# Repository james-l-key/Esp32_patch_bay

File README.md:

# Esp32_Patch_Bay

## Warning! 

This project is in active hardware and software development. Things may change drastically at a moments notice.

An 8-pedal mono guitar patch bay controlled by an ESP32-S3, allowing dynamic reconfiguration of guitar pedal signal chains via a user interface with an OLED display and push buttons. The project uses analog multiplexers (CD4051B, ADG419BN) and op-amps (TL072) to route audio signals, controlled through shift registers (74HC595) interfaced with the ESP32-S3. The schematic is designed in KiCad 9.0, and the firmware is developed using the ESP-IDF framework.

## Table of Contents
- [Esp32\_Patch\_Bay](#esp32_patch_bay)
  - [Table of Contents](#table-of-contents)
  - [Features](#features)
  - [Hardware](#hardware)
  - [Software](#software)
  - [Installation](#installation)
  - [Usage](#usage)
  - [Project Structure](#project-structure)
  - [Contributing](#contributing)
  - [Issues](#issues)
  - [License](#license)
  - [Acknowledgements](#acknowledgements)

## Features
- **Dynamic Signal Routing**: Reconfigure the signal chain for up to 8 mono guitar pedals using a 9x8 matrix.
- **User Interface**: SSD1306/SH1106 OLED display for configuration feedback, with three push buttons (Program, Pedal 1, Pedal 2) and a Program Mode LED.
- **Low-Latency Audio**: CD4051B and ADG419BN analog multiplexers and TL072 op-amps ensure clean, buffered audio signal routing.
- **ESP32-S3 Control**: High-performance microcontroller for real-time control, programmed via ESP-IDF.
- **Extensible Design**: Easily scalable to support more pedals by adding multiplexers and shift registers.
- **Open Source**: Full schematic (`circuit.kicad_sch`), PCB layout, and firmware provided.

## Hardware
The patch bay is built around an **ESP32-S3** microcontroller and uses analog multiplexers for audio routing. For the complete hardware details, including the **schematic**, **PCB layout**, and **Bill of Materials (BOM)**, please see the dedicated [hardware repository](https://github.com/your-username/esp32_patch_bay_hardware).

## Software
The firmware is written in C using the **ESP-IDF** framework (v5.1 or later) for the ESP32-S3. Key components include:
- **Matrix Control**: `matrix.c` manages the 9x8 signal routing matrix, interfacing with 74HC595 shift registers to set analog switch states.
- **OLED Driver**: Displays the current signal chain and configuration status.
- **Button Handling**: Debounced inputs for Program, Pedal 1, and Pedal 2 buttons to navigate and set configurations.
- **LED Control**: Toggles the Program Mode LED based on user interaction.

### Dependencies
- **ESP-IDF**: Install ESP-IDF v5.1 or later (see [Espressif Documentation](https://docs.espressif.com/projects/esp-idf/en/latest/esp32s3/)).
- **KiCad 9.0**: For viewing/editing the schematic (`circuit.kicad_sch`).
- **I2C Library**: For SSD1306/SH1106 OLED communication (included in ESP-IDF).
- **GPIO Drivers**: Standard ESP-IDF GPIO functions for buttons, LED, and shift registers.

## Installation
### Prerequisites
- **Hardware**:
  - ESP32-S3 development board or custom PCB with the components listed above.
  - 1/4” mono jacks, buttons, LED, resistors (220Ω for LED, 4.7kΩ for pull-ups), and capacitors.
  - ±9V power supply or charge pump circuit.
- **Software**:
  - [ESP-IDF](https://docs.espressif.com/projects/esp-idf/en/latest/esp32s3/get-started/index.html) installed and configured.
  - [KiCad 9.0](https://www.kicad.org/download/) for schematic/PCB design.
  - A C compiler (e.g., `xtensa-esp32s3-elf-gcc`) included with ESP-IDF.
  - Python 3 for ESP-IDF build scripts.

### Steps
1. **Clone the Repository**:
   ```bash
   git clone [https://github.com/phi/Esp32_patch_bay.git](https://github.com/phi/Esp32_patch_bay.git)
   cd Esp32_patch_bay
   
2. **Set Up ESP-IDF**:
        Follow the ESP-IDF Getting Started Guide.
        Ensure the idf.py tool is accessible in your terminal.

3. **Build the Firmware**:
    ```bash
    idf.py set-target esp32s3
    idf.py build
   
5. **Flash the Firmware**:

    Connect the ESP32-S3 to your computer via USB.
    Flash the firmware:
    ```bash

        idf.py -p /dev/ttyUSB0 flash

  Replace /dev/ttyUSB0 with your serial port (e.g., COM3 on Windows).

  6. **Open the Schematic**:
        Launch KiCad 9.0.
        Open circuit.kicad_sch from the repository root.
        Verify connections and assign footprints for PCB layout.

   7. **Assemble the Hardware**:
        Solder components onto a PCB or prototype board based on the schematic.
        Connect 1/4” jacks to guitar, pedals, and amplifier.
        Power the circuit with +3.3V and ±9V supplies.

## Usage

  **Power On**:
        Connect the patch bay to power (+3.3V, ±9V).
        The OLED displays the current signal chain (e.g., Guitar → Pedal 1 → Pedal 2 → Amp).

  **Program Mode**:
        Press the Program button (SW1) to enter Program Mode (LED1 lights up).
        Use Pedal 1 (SW2) and Pedal 2 (SW3) buttons to select the desired signal path.
        Press Program again to save and exit.

  **Signal Routing**:
        The ESP32-S3 updates the 74HC595 shift registers, which set the analog switches to route the audio signal.
        TL072 op-amps buffer the input and output to maintain signal integrity.

  **Monitor**:
        Use the OLED to confirm the signal chain.
        Check the serial output (via idf.py monitor) for debugging.

***Example Signal Chains***

  * Bypass: Guitar → Amp.
  * Single Pedal: Guitar → Pedal 1 → Amp.
  * Dual Pedal: Guitar → Pedal 1 → Pedal 7 → Amp or Guitar → Pedal 2 → Pedal 1 → Amp.

## Project Structure

```md
Esp32_patch_bay/
├── circuit.kicad_sch        # KiCad 9.0 schematic for 3x3 matrix (scalable to 9x8)
├── main/
│   ├── main.c               # Entry point for ESP-IDF firmware
│   ├── matrix.c             # Signal routing matrix control
│   ├── matrix.h             # Header for matrix functions
│   ├── oled.c               # OLED display driver
│   ├── oled.h               # Header for OLED functions
├── CMakeLists.txt           # ESP-IDF project configuration
├── README.md                # This file
├── LICENSE                  # License file (e.g., MIT)
└── docs/
    ├── HARDWARE.md          # Detailed hardware setup
    ├── SOFTWARE.md          # Firmware development guide
    ├── TROUBLESHOOTING.md   # Common issues and solutions
```
## Scaling to 8 Pedals

**The current schematic implements a 9x8 matrix (Guitar In, Amp Out, and 8 pedals In/Out).**

## Contributing

**Contributions are welcome! To contribute**:

  Fork the repository.
  Create a branch (git checkout -b feature/your-feature).
  Commit changes (git commit -m "Add your feature").
  Push to the branch (git push origin feature/your-feature).
  Open a Pull Request.

## Issues

  Report bugs or suggest features via the Issues tab.
  Include reproduction steps and relevant logs (e.g., idf.py monitor output).

## License

This project is licensed under the MIT License. See the [LICENSE](LICENSE) file for details.

## Acknowledgements

  Espressif Systems for the ESP-IDF framework and ESP32-S3.
  KiCad for open-source EDA tools.
  Community: Inspiration from guitar pedalboard designs and open-source hardware projects.

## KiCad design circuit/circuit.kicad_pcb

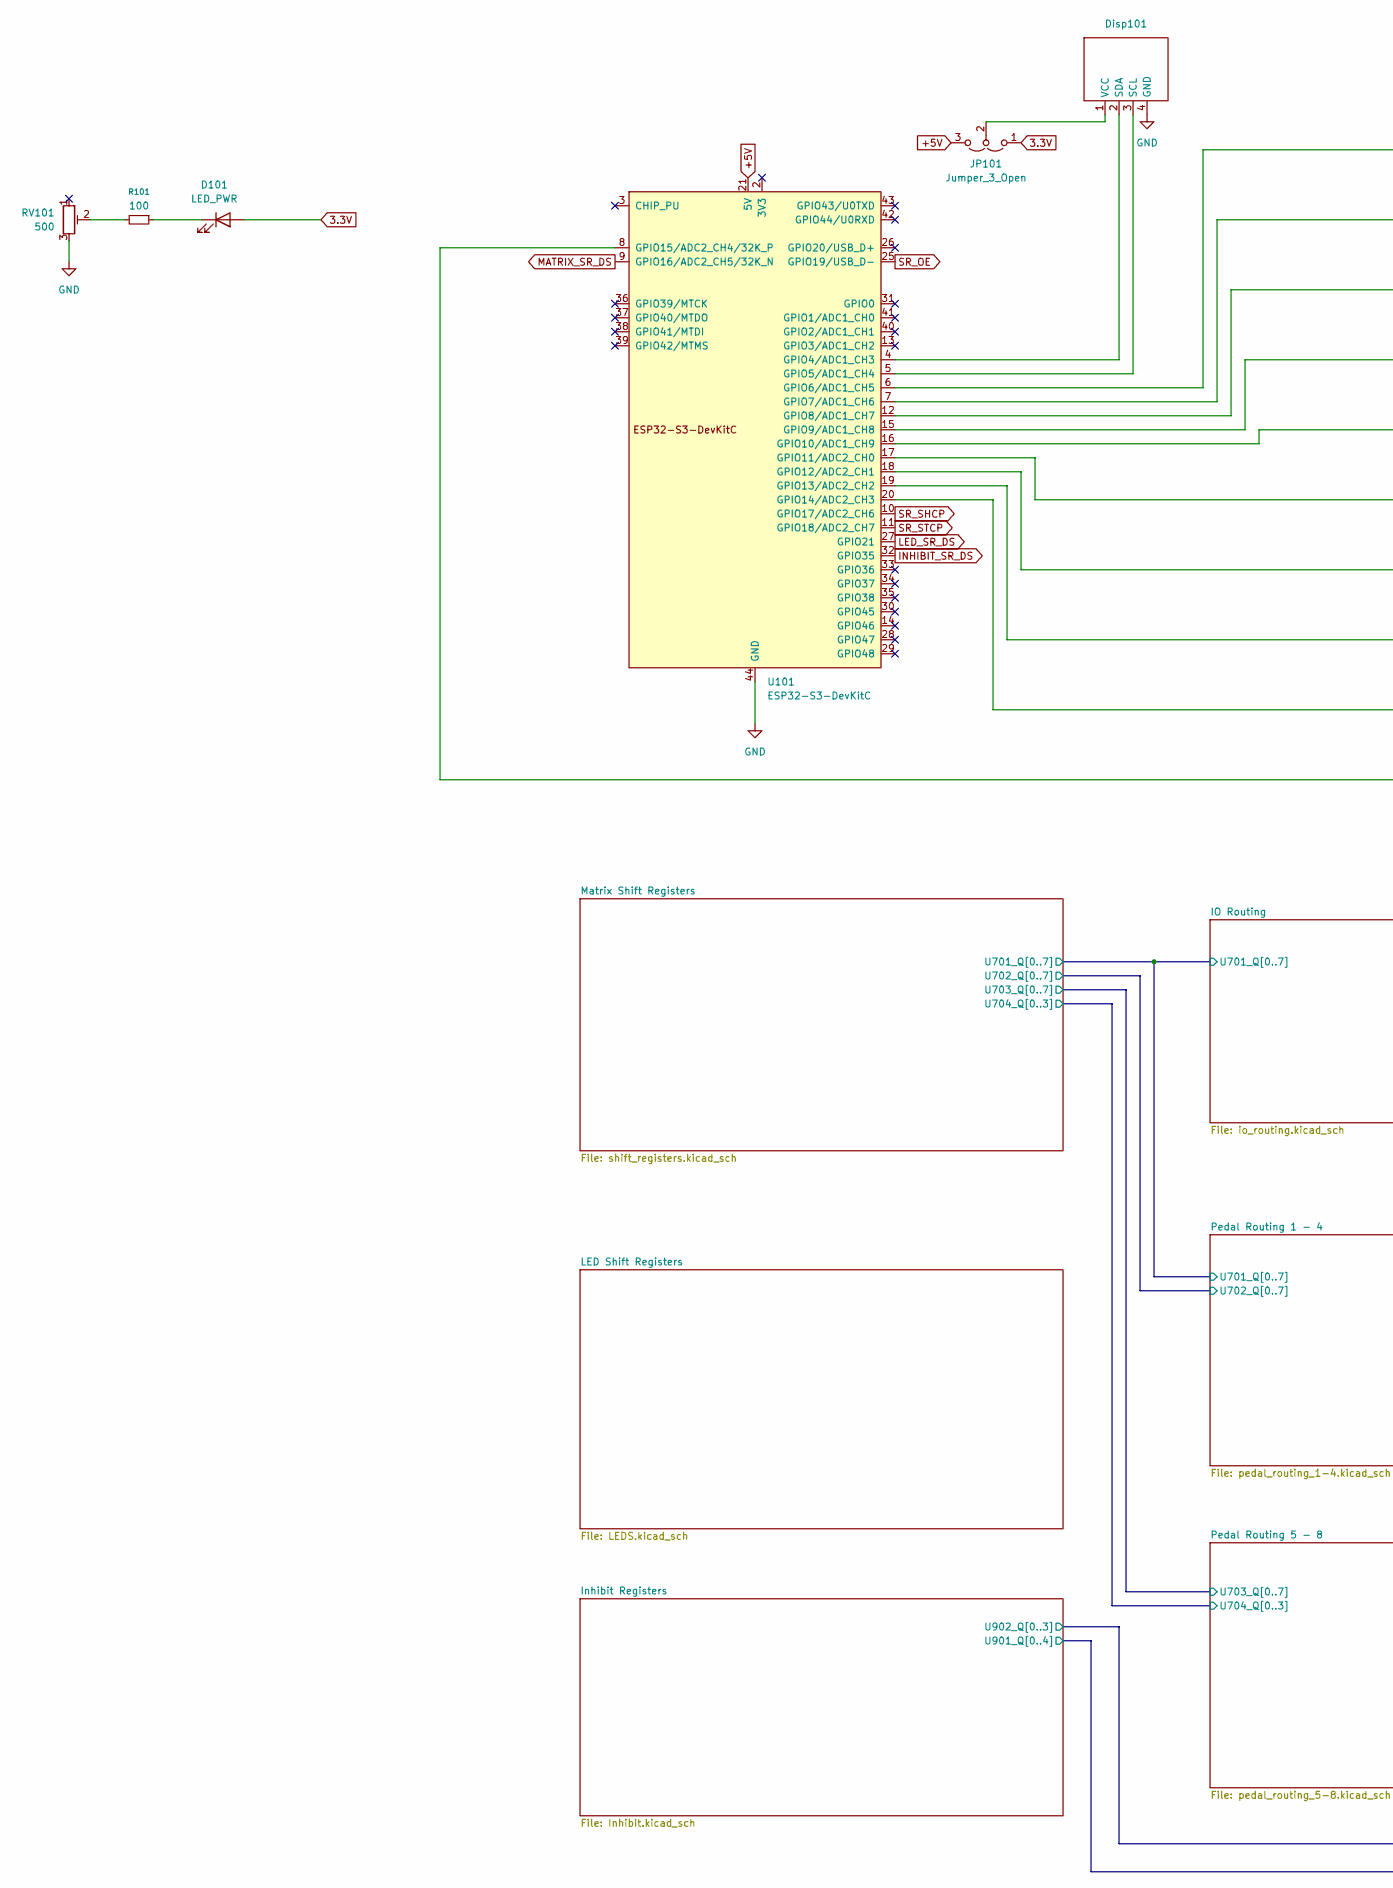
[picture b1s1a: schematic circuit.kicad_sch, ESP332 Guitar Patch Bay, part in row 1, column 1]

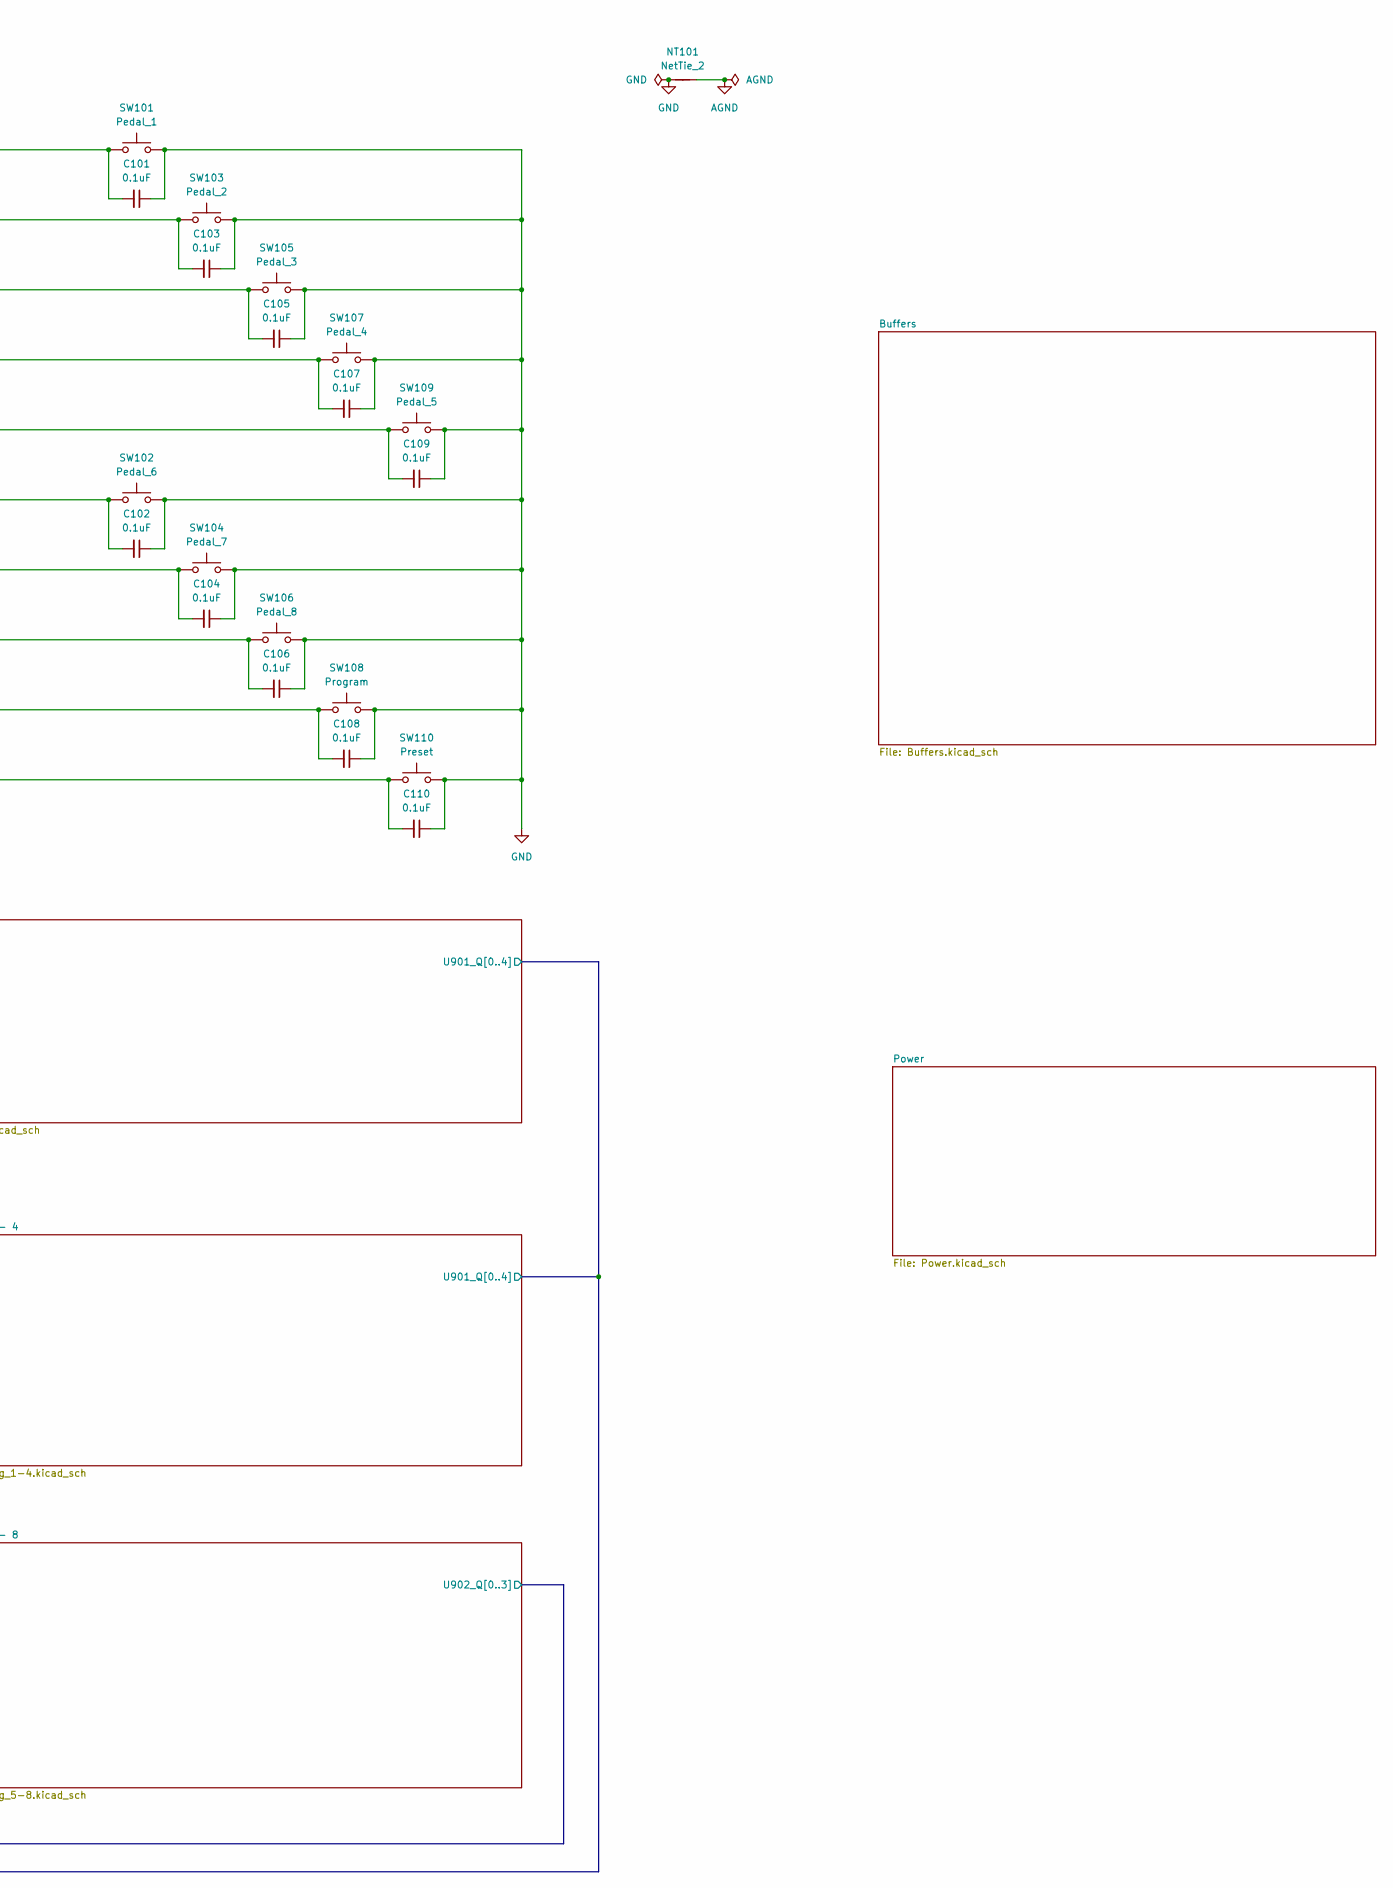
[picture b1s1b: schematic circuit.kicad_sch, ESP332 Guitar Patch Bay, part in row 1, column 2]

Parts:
C101, C102, C103, C104, C105, C106, C107, C108, C109, C110: 0.1uF; C_Disc_D5.0mm_W2.5mm_P2.50mm
D101: LED_PWR; PinHeader_1x02_P2.54mm_Vertical
Disp101: PinHeader_1x04_P2.54mm_Vertical
JP101: Jumper_3_Open; PinSocket_1x03_P2.54mm_Vertical
NT101: NetTie_2; NetTie-2_THT_Pad1.0mm
R101: 100; R_Axial_DIN0207_L6.3mm_D2.5mm_P7.62mm_Horizontal
RV101: 500; Potentiometer_Bourns_3339P_Vertical
SW101: Pedal_1; PinHeader_1x02_P2.54mm_Vertical
SW102: Pedal_6; PinHeader_1x02_P2.54mm_Vertical
SW103: Pedal_2; PinHeader_1x02_P2.54mm_Vertical
SW104: Pedal_7; PinHeader_1x02_P2.54mm_Vertical
SW105: Pedal_3; PinHeader_1x02_P2.54mm_Vertical
SW106: Pedal_8; PinHeader_1x02_P2.54mm_Vertical
SW107: Pedal_4; PinHeader_1x02_P2.54mm_Vertical
SW108: Program; PinHeader_1x02_P2.54mm_Vertical
SW109: Pedal_5; PinHeader_1x02_P2.54mm_Vertical
SW110: Preset; PinHeader_1x02_P2.54mm_Vertical
U101: ESP32-S3-DevKitC

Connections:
3.3V: D101.2 (A), JP101.1 (A); also elsewhere on the board
+5V: JP101.3 (B), U101.21 (5V); also elsewhere on the board
AGND: NT101.2; also elsewhere on the board
GND: C101.1, C102.1, C103.1, C104.1, C105.1, C106.1, C107.1, C108.1, C109.1, C110.1, Disp101.4 (GND), NT101.1, RV101.3, SW101.2, SW102.2, SW103.2, SW104.2, SW105.2, SW106.2, SW107.2, SW108.2, SW109.2, SW110.2, U101.22 (GND), U101.23 (GND), U101.24 (GND), U101.44 (GND); also elsewhere on the board
INHIBIT_SR_DS: U101.32 (GPIO35); also elsewhere on the board
LED_SR_DS: U101.27 (GPIO21); also elsewhere on the board
MATRIX_SR_DS: U101.9 (GPIO16/ADC2_CH5/32K_N); also elsewhere on the board
unnamed: D101.1 (K), R101.1
unnamed: Disp101.3 (SCL), U101.5 (GPIO5/ADC1_CH4)
unnamed: Disp101.2 (SDA), U101.4 (GPIO4/ADC1_CH3)
unnamed: Disp101.1 (VCC), JP101.2 (C)
unnamed: R101.2, RV101.2
unnamed: C101.2, SW101.1, U101.6 (GPIO6/ADC1_CH5)
unnamed: C103.2, SW103.1, U101.7 (GPIO7/ADC1_CH6)
unnamed: C105.2, SW105.1, U101.12 (GPIO8/ADC1_CH7)
unnamed: C107.2, SW107.1, U101.15 (GPIO9/ADC1_CH8)
unnamed: C109.2, SW109.1, U101.16 (GPIO10/ADC1_CH9)
unnamed: C102.2, SW102.1, U101.17 (GPIO11/ADC2_CH0)
unnamed: C104.2, SW104.1, U101.18 (GPIO12/ADC2_CH1)
unnamed: C106.2, SW106.1, U101.19 (GPIO13/ADC2_CH2)
unnamed: C108.2, SW108.1, U101.20 (GPIO14/ADC2_CH3)
unnamed: C110.2, SW110.1, U101.8 (GPIO15/ADC2_CH4/32K_P)
SR_OE: U101.25 (GPIO19/USB_D-); also elsewhere on the board
SR_SHCP: U101.10 (GPIO17/ADC2_CH6); also elsewhere on the board
SR_STCP: U101.11 (GPIO18/ADC2_CH7); also elsewhere on the board

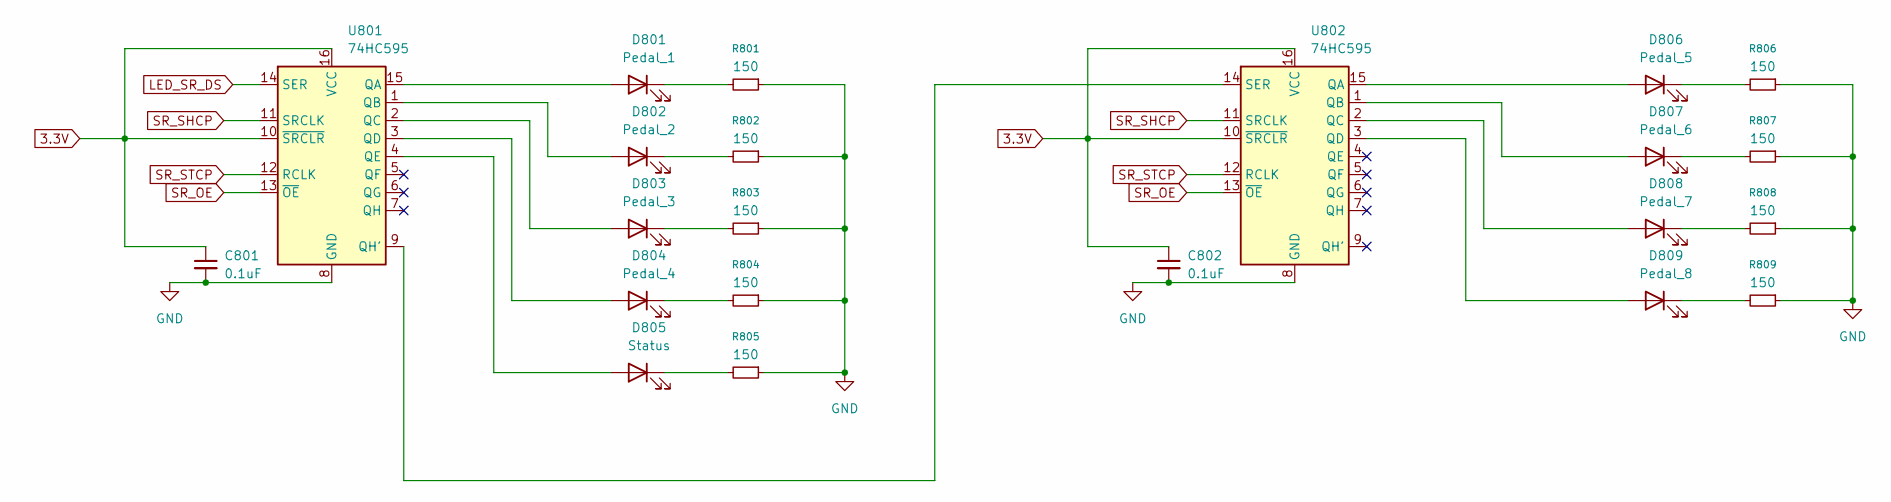
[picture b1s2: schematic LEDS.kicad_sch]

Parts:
C801, C802: 0.1uF; C_Disc_D5.0mm_W2.5mm_P2.50mm
D801: Pedal_1; PinHeader_1x02_P2.54mm_Vertical
D802: Pedal_2; PinHeader_1x02_P2.54mm_Vertical
D803: Pedal_3; PinHeader_1x02_P2.54mm_Vertical
D804: Pedal_4; PinHeader_1x02_P2.54mm_Vertical
D805: Status; PinHeader_1x02_P2.54mm_Vertical
D806: Pedal_5; PinHeader_1x02_P2.54mm_Vertical
D807: Pedal_6; PinHeader_1x02_P2.54mm_Vertical
D808: Pedal_7; PinHeader_1x02_P2.54mm_Vertical
D809: Pedal_8; PinHeader_1x02_P2.54mm_Vertical
R801, R802, R803, R804, R805, R806, R807, R808, R809: 150; R_Axial_DIN0207_L6.3mm_D2.5mm_P7.62mm_Horizontal
U801, U802: 74HC595; DIP-16_W7.62mm

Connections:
3.3V: C801.1, C802.1, U801.10 (~SRCLR), U801.16 (VCC), U802.10 (~SRCLR), U802.16 (VCC); also elsewhere on the board
GND: C801.2, C802.2, R801.1, R802.1, R803.1, R804.1, R805.1, R806.1, R807.1, R808.1, R809.1, U801.8 (GND), U802.8 (GND); also elsewhere on the board
LED_SR_DS: U801.14 (SER); also elsewhere on the board
unnamed: D801.2 (A), U801.15 (QA)
unnamed: D801.1 (K), R801.2
unnamed: D802.2 (A), U801.1 (QB)
unnamed: D802.1 (K), R802.2
unnamed: D803.2 (A), U801.2 (QC)
unnamed: D803.1 (K), R803.2
unnamed: D804.2 (A), U801.3 (QD)
unnamed: D804.1 (K), R804.2
unnamed: D805.2 (A), U801.4 (QE)
unnamed: D805.1 (K), R805.2
unnamed: D806.2 (A), U802.15 (QA)
unnamed: D806.1 (K), R806.2
unnamed: D807.2 (A), U802.1 (QB)
unnamed: D807.1 (K), R807.2
unnamed: D808.2 (A), U802.2 (QC)
unnamed: D808.1 (K), R808.2
unnamed: D809.2 (A), U802.3 (QD)
unnamed: D809.1 (K), R809.2
unnamed: U801.9 (QH'), U802.14 (SER)
SR_OE: U801.13 (~OE), U802.13 (~OE); also elsewhere on the board
SR_SHCP: U801.11 (SRCLK), U802.11 (SRCLK); also elsewhere on the board
SR_STCP: U801.12 (RCLK), U802.12 (RCLK); also elsewhere on the board

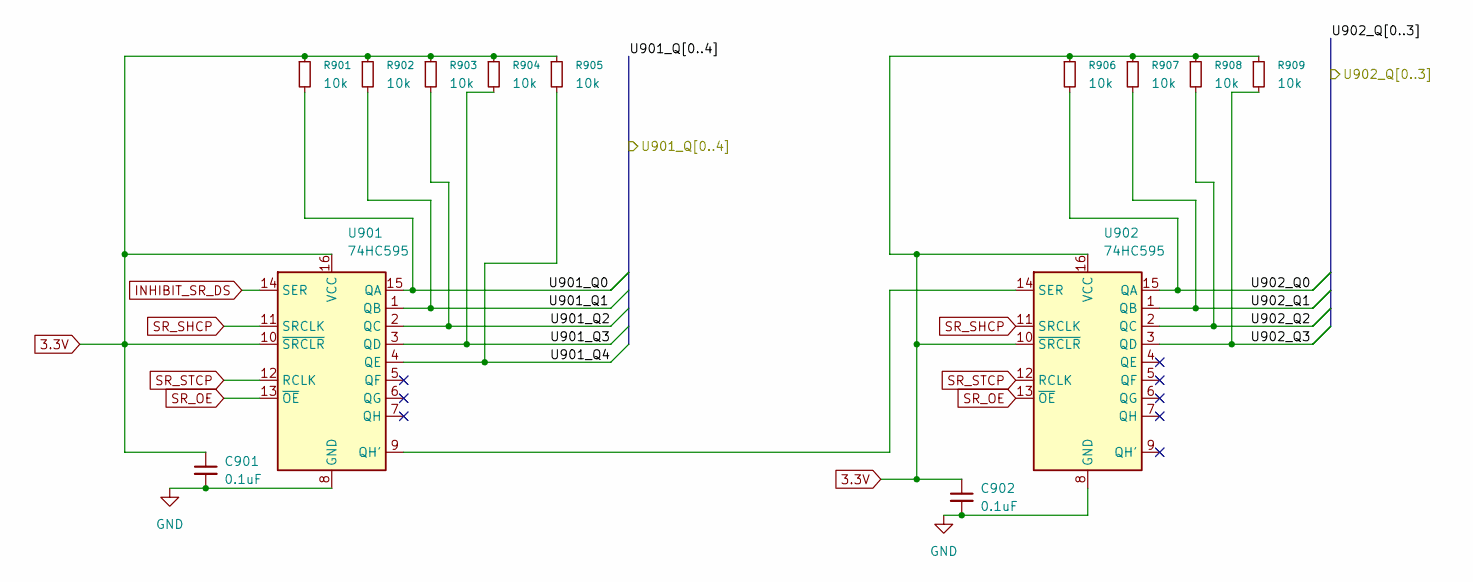
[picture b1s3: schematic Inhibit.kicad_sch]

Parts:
C901, C902: 0.1uF; C_Disc_D5.0mm_W2.5mm_P2.50mm
R901, R902, R903, R904, R905, R906, R907, R908, R909: 10k; R_Axial_DIN0207_L6.3mm_D2.5mm_P7.62mm_Horizontal
U901, U902: 74HC595; DIP-16_W7.62mm

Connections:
3.3V: C901.1, C902.1, R901.1, R902.1, R903.1, R904.1, R905.1, R906.1, R907.1, R908.1, R909.1, U901.10 (~SRCLR), U901.16 (VCC), U902.10 (~SRCLR), U902.16 (VCC); also elsewhere on the board
/IO Routing/U901_Q0: R901.2, U901.15 (QA); also elsewhere on the board
/IO Routing/U901_Q1: R902.2, U901.1 (QB); also elsewhere on the board
/IO Routing/U901_Q2: R903.2, U901.2 (QC); also elsewhere on the board
/IO Routing/U901_Q3: R904.2, U901.3 (QD); also elsewhere on the board
/IO Routing/U901_Q4: R905.2, U901.4 (QE); also elsewhere on the board
/Inhibit Registers/U902_Q0: R906.2, U902.15 (QA); also elsewhere on the board
/Inhibit Registers/U902_Q1: R907.2, U902.1 (QB); also elsewhere on the board
/Inhibit Registers/U902_Q2: R908.2, U902.2 (QC); also elsewhere on the board
/Inhibit Registers/U902_Q3: R909.2, U902.3 (QD); also elsewhere on the board
GND: C901.2, C902.2, U901.8 (GND), U902.8 (GND); also elsewhere on the board
INHIBIT_SR_DS: U901.14 (SER); also elsewhere on the board
unnamed: U901.9 (QH'), U902.14 (SER)
SR_OE: U901.13 (~OE), U902.13 (~OE); also elsewhere on the board
SR_SHCP: U901.11 (SRCLK), U902.11 (SRCLK); also elsewhere on the board
SR_STCP: U901.12 (RCLK), U902.12 (RCLK); also elsewhere on the board

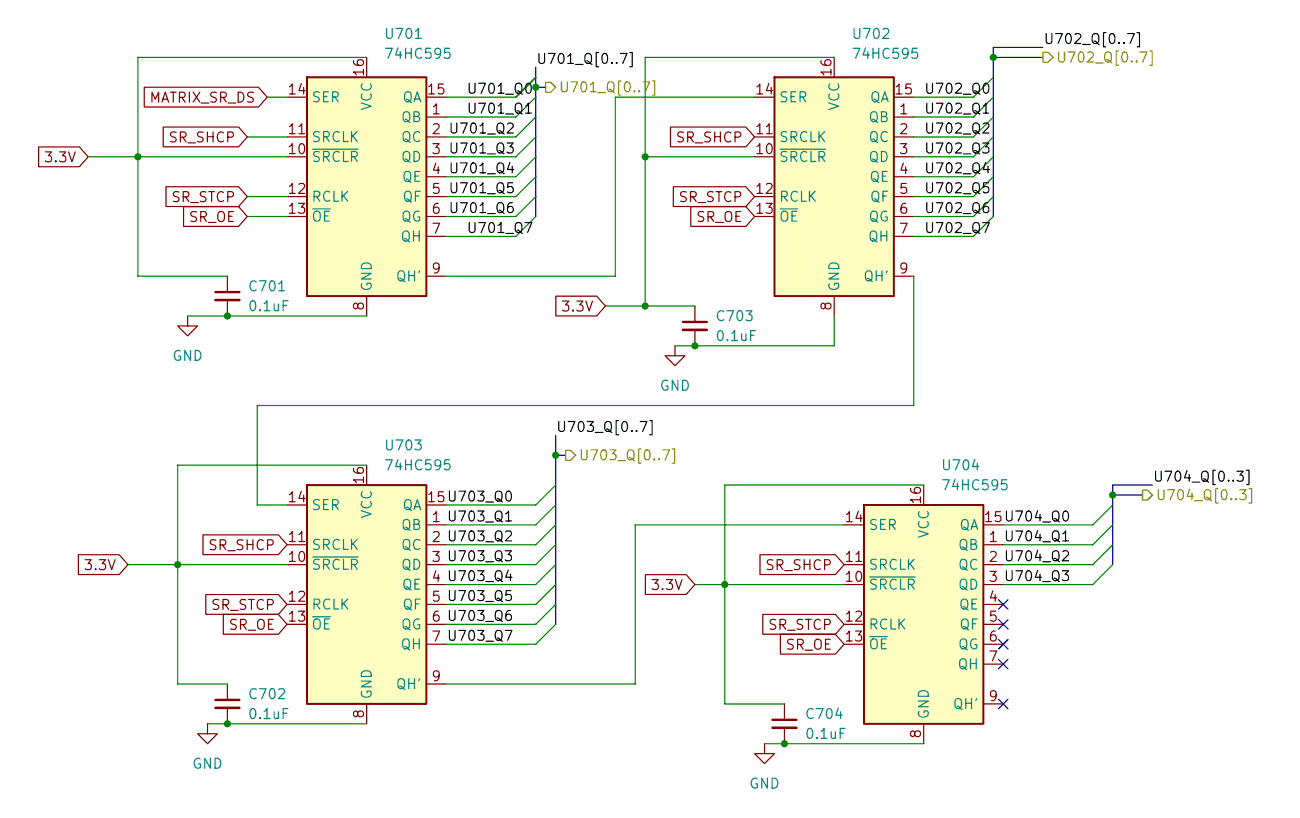
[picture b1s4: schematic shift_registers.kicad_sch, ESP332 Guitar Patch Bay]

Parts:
C701, C702, C703, C704: 0.1uF; C_Disc_D5.0mm_W2.5mm_P2.50mm
U701, U702, U703, U704: 74HC595; DIP-16_W7.62mm

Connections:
3.3V: C701.1, C702.1, C703.1, C704.1, U701.10 (~SRCLR), U701.16 (VCC), U702.10 (~SRCLR), U702.16 (VCC), U703.10 (~SRCLR), U703.16 (VCC), U704.10 (~SRCLR), U704.16 (VCC); also elsewhere on the board
/IO Routing/U701_Q0: U701.15 (QA); also elsewhere on the board
/IO Routing/U701_Q1: U701.1 (QB); also elsewhere on the board
/IO Routing/U701_Q2: U701.2 (QC); also elsewhere on the board
/IO Routing/U701_Q3: U701.3 (QD); also elsewhere on the board
/IO Routing/U701_Q4: U701.4 (QE); also elsewhere on the board
/IO Routing/U701_Q5: U701.5 (QF); also elsewhere on the board
/IO Routing/U701_Q6: U701.6 (QG); also elsewhere on the board
/IO Routing/U701_Q7: U701.7 (QH); also elsewhere on the board
/Matrix Shift Registers/U702_Q0: U702.15 (QA); also elsewhere on the board
/Matrix Shift Registers/U702_Q1: U702.1 (QB); also elsewhere on the board
/Matrix Shift Registers/U702_Q2: U702.2 (QC); also elsewhere on the board
/Matrix Shift Registers/U702_Q3: U702.3 (QD); also elsewhere on the board
/Matrix Shift Registers/U702_Q4: U702.4 (QE); also elsewhere on the board
/Matrix Shift Registers/U702_Q5: U702.5 (QF); also elsewhere on the board
/Matrix Shift Registers/U702_Q6: U702.6 (QG); also elsewhere on the board
/Matrix Shift Registers/U702_Q7: U702.7 (QH); also elsewhere on the board
/Matrix Shift Registers/U703_Q0: U703.15 (QA); also elsewhere on the board
/Matrix Shift Registers/U703_Q1: U703.1 (QB); also elsewhere on the board
/Matrix Shift Registers/U703_Q2: U703.2 (QC); also elsewhere on the board
/Matrix Shift Registers/U703_Q3: U703.3 (QD); also elsewhere on the board
/Matrix Shift Registers/U703_Q4: U703.4 (QE); also elsewhere on the board
/Matrix Shift Registers/U703_Q5: U703.5 (QF); also elsewhere on the board
/Matrix Shift Registers/U703_Q6: U703.6 (QG); also elsewhere on the board
/Matrix Shift Registers/U703_Q7: U703.7 (QH); also elsewhere on the board
/Matrix Shift Registers/U704_Q0: U704.15 (QA); also elsewhere on the board
/Matrix Shift Registers/U704_Q1: U704.1 (QB); also elsewhere on the board
/Matrix Shift Registers/U704_Q2: U704.2 (QC); also elsewhere on the board
/Matrix Shift Registers/U704_Q3: U704.3 (QD); also elsewhere on the board
GND: C701.2, C702.2, C703.2, C704.2, U701.8 (GND), U702.8 (GND), U703.8 (GND), U704.8 (GND); also elsewhere on the board
MATRIX_SR_DS: U701.14 (SER); also elsewhere on the board
unnamed: U701.9 (QH'), U702.14 (SER)
unnamed: U702.9 (QH'), U703.14 (SER)
unnamed: U703.9 (QH'), U704.14 (SER)
SR_OE: U701.13 (~OE), U702.13 (~OE), U703.13 (~OE), U704.13 (~OE); also elsewhere on the board
SR_SHCP: U701.11 (SRCLK), U702.11 (SRCLK), U703.11 (SRCLK), U704.11 (SRCLK); also elsewhere on the board
SR_STCP: U701.12 (RCLK), U702.12 (RCLK), U703.12 (RCLK), U704.12 (RCLK); also elsewhere on the board

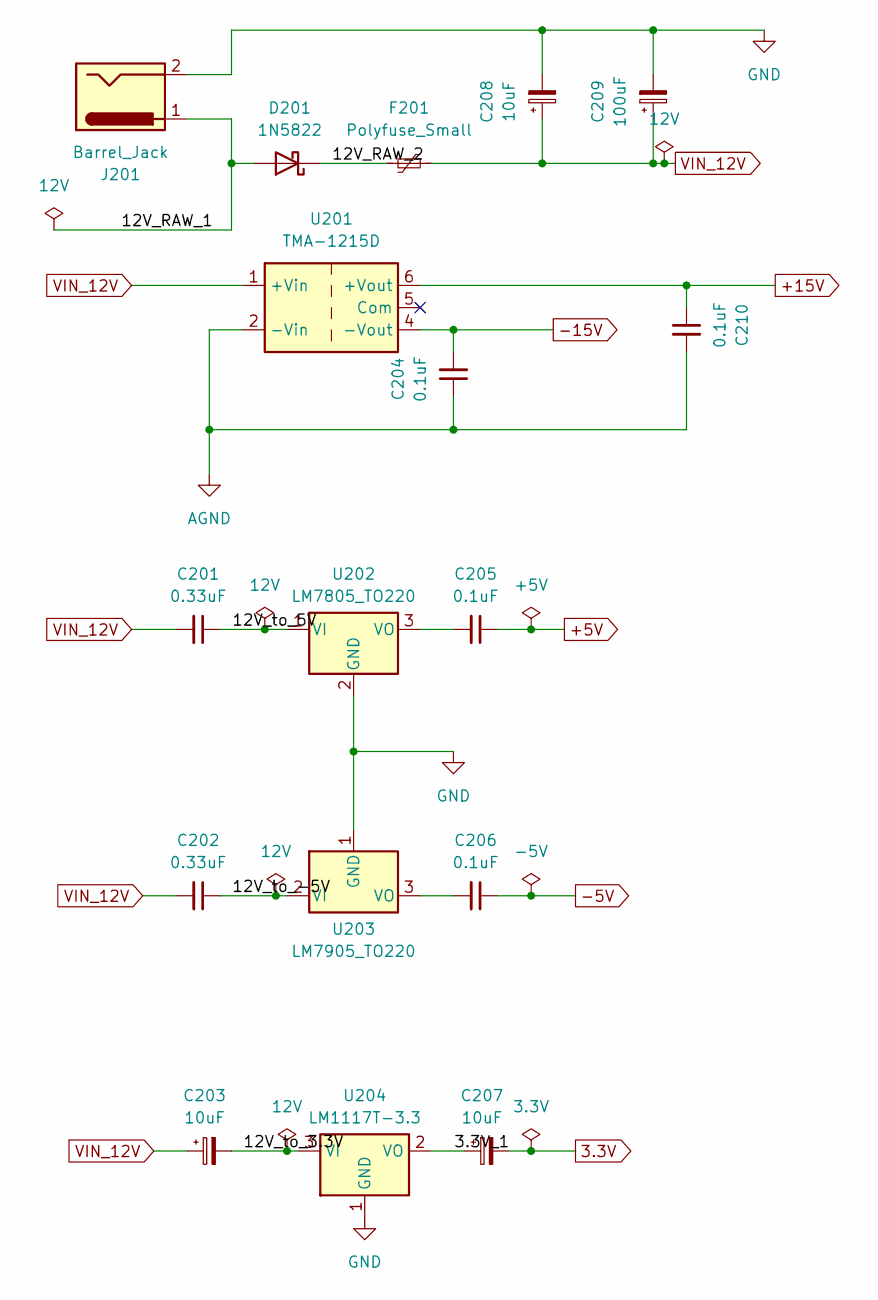
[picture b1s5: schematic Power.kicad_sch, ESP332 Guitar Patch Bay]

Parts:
C201, C202: 0.33uF; C_Disc_D5.0mm_W2.5mm_P2.50mm
C203, C207, C208: 10uF; CP_Radial_D5.0mm_P2.50mm
C204, C205, C206, C210: 0.1uF; C_Disc_D5.0mm_W2.5mm_P2.50mm
C209: 100uF; CP_Radial_D5.0mm_P2.50mm
D201: 1N5822; D_DO-41_SOD81_P10.16mm_Horizontal
F201: Polyfuse_Small; Fuse_Bourns_MF-RG500
J201: Barrel_Jack; BarrelJack_CUI_PJ-063AH_Horizontal_CircularHoles
U201: TMA-1215D; Converter_DCDC_TRACO_TMA-05xxD_12xxD_Dual_THT
U202: LM7805_TO220; TO-220-3_Vertical
U203: LM7905_TO220; TO-220-3_Vertical
U204: LM1117T-3.3; TO-220-3_Vertical

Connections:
3.3V: C207.2; also elsewhere on the board
+5V: C205.1; also elsewhere on the board
+15V: C210.1, U201.6 (+Vout); also elsewhere on the board
-5V: C206.1; also elsewhere on the board
-15V: C204.2, U201.4 (-Vout); also elsewhere on the board
/Power/3.3V_1: C207.1, U204.2 (VO)
/Power/12V_RAW_1: D201.2 (A), J201.1
/Power/12V_RAW_2: D201.1 (K), F201.2
/Power/12V_to_3.3V: C203.2, U204.3 (VI)
/Power/12V_to_5V: C201.1, U202.1 (VI)
/Power/12V_to_-5V: C202.1, U203.2 (VI)
AGND: C204.1, C210.2, U201.2 (-Vin); also elsewhere on the board
GND: C208.2, C209.2, J201.2, U202.2 (GND), U203.1 (GND), U204.1 (GND); also elsewhere on the board
unnamed: C205.2, U202.3 (VO)
unnamed: C206.2, U203.3 (VO)
VIN_12V: C201.2, C202.2, C203.1, C208.1, C209.1, F201.1, U201.1 (+Vin)
